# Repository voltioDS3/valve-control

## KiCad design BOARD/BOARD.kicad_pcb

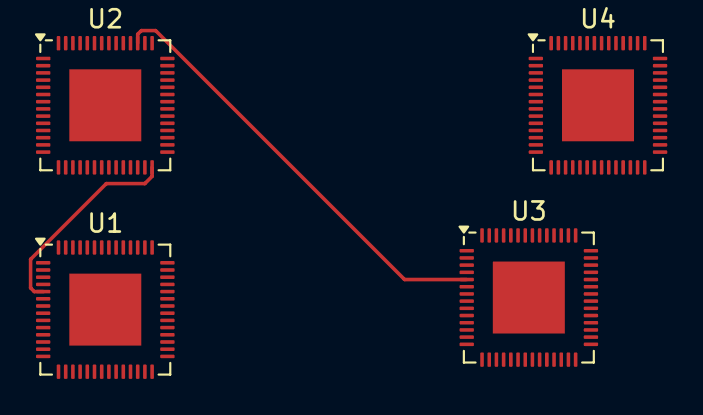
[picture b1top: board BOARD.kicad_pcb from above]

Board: 2 copper layers, 4 parts (0 on the bottom side), 8 nets.

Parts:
U1, U2, U3, U4: ESP32-S3; QFN-56-1EP_7x7mm_P0.4mm_EP4x4mm

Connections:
/triac-circuit1/test-label: U2.45 (MTDO), U3.5 (GPIO0)
/triac-circuit/test-label: U1.5 (GPIO0), U2.28 (SPICS1)
unnamed: U2.2 (VDD3P3), U2.3 (VDD3P3)
unnamed: U2.55 (VDDA), U2.56 (VDDA)
unnamed: U3.2 (VDD3P3), U3.3 (VDD3P3)
unnamed: U3.55 (VDDA), U3.56 (VDDA)
unnamed: U4.2 (VDD3P3), U4.3 (VDD3P3)
unnamed: U4.55 (VDDA), U4.56 (VDDA)

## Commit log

2024-12-12 added class valve and dashboard implementation
2024-12-12 variable optimization
2024-12-12 global variable test
2024-12-13 fix check interval
2024-12-13 test
2024-12-13 added NTP server and RTC reads, also added functionallity to work with the valve object
2024-12-13 checkSchedules on main function
2024-12-13 implemented schedule creation
2024-12-13 you can now add schedules and they will show up in website, also made whole dashboard easier to view in phones
2024-12-15 fix schedule logic
2024-12-15 added dns so you can acces via valvulas.local
2024-12-15 schedules save in flash, also you can read the flash at setup so no schedule is lost when power goes down
2024-12-20 working on deleting schedules
2024-12-20 added debug preprocesor
2024-12-22 added remove schedule and pcb schematic, TODO: rewrite valve states considering the remove case
